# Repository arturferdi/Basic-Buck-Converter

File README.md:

# Basic-Buck-Converter
A Super Simple Buck Converter Design with NE555 as a PWM Generator. You can use this as your project, especially you are a student from PENS. Because this is my old project at smt4. Contact me if you want to ask something. Soon I'll give you the formula for some parameters

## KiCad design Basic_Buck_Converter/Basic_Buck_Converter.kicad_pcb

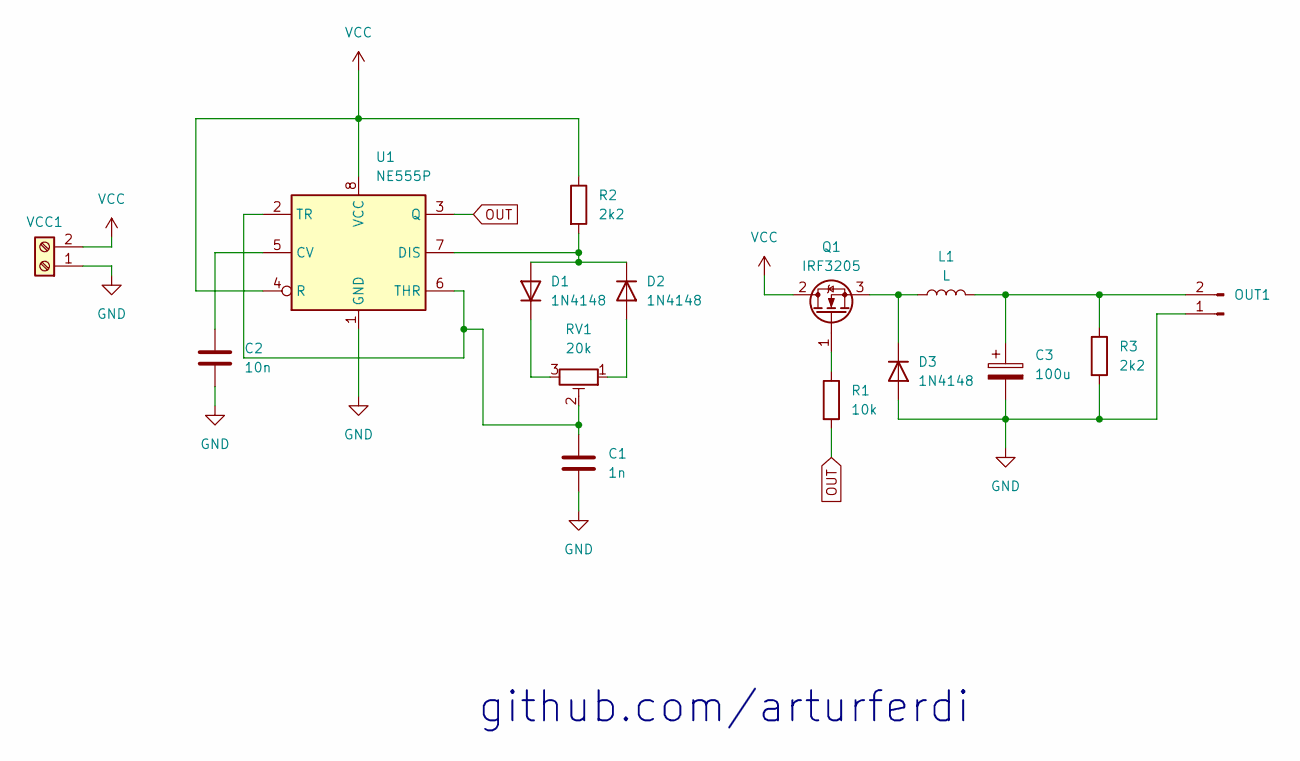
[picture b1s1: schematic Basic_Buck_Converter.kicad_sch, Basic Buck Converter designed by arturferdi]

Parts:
C1: 1n; C_Rect_L7.0mm_W2.0mm_P5.00mm
C2: 10n; C_Rect_L7.0mm_W2.0mm_P5.00mm
C3: 100u; CP_Radial_D4.0mm_P2.00mm
D1, D2, D3: 1N4148; D_DO-35_SOD27_P7.62mm_Horizontal
L1: L; L_Toroid_Vertical_L13.0mm_W6.5mm_P5.60mm
OUT1: Conn_01x02_Pin; PinHeader_1x02_P2.54mm_Vertical
Q1: IRF3205; TO-220-3_Vertical
R1: 10k; R_Axial_DIN0309_L9.0mm_D3.2mm_P5.08mm_Vertical
R2, R3: 2k2; R_Axial_DIN0309_L9.0mm_D3.2mm_P5.08mm_Vertical
RV1: 20k; Potentiometer_Runtron_RM-065_Vertical
U1: NE555P; DIP-8_W7.62mm
VCC1: Screw_Terminal_01x02; TerminalBlock_MetzConnect_Type073_RT02602HBLU_1x02_P5.08mm_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

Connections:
GND: C1.2, C2.2, C3.2, D3.2 (A), OUT1.1, R3.2, U1.1 (GND), VCC1.1
unnamed: D1.2 (A), D2.1 (K), R2.2, U1.7 (DIS)
unnamed: D1.1 (K), RV1.3
unnamed: D2.2 (A), RV1.1
unnamed: D3.1 (K), L1.1, Q1.3 (S)
unnamed: C3.1, L1.2, OUT1.2, R3.1
unnamed: Q1.1 (G), R1.1
unnamed: C2.1, U1.5 (CV)
unnamed: C1.1, RV1.2, U1.2 (TR), U1.6 (THR)
OUT: R1.2, U1.3 (Q)
VCC: Q1.2 (D), R2.1, U1.4 (R), U1.8 (VCC), VCC1.2

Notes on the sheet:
github.com/arturferdi

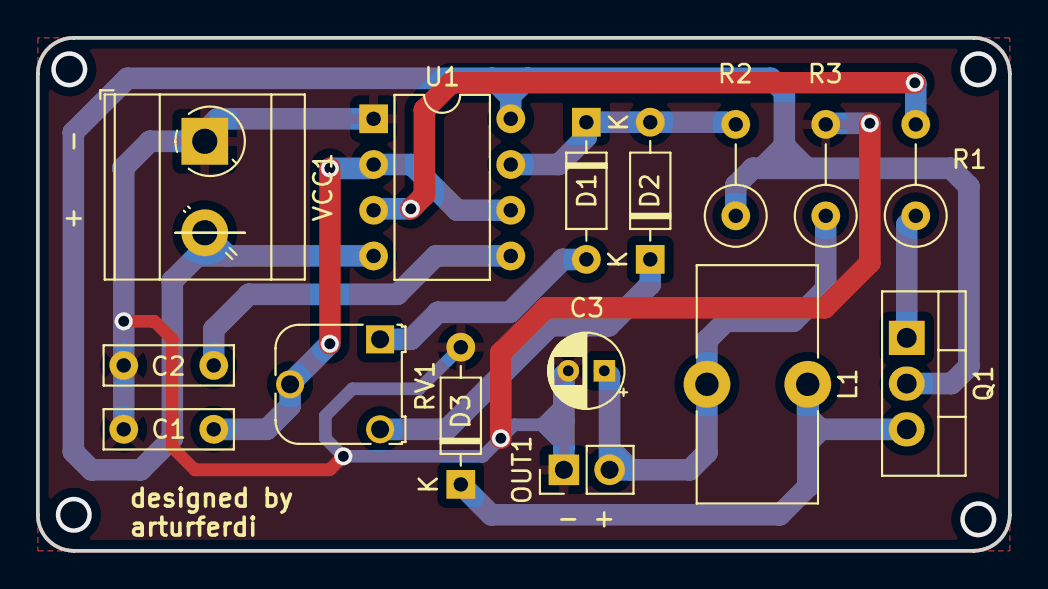
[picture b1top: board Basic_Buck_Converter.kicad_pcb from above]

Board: 2 copper layers, 54.0 x 28.5 mm, 15 parts (0 on the bottom side), 11 nets.

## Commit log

2025-06-26 add kicad pro
